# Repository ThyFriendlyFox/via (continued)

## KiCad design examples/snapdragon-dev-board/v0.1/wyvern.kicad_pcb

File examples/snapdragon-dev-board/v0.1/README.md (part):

# Wyvern — board prototype v0.1

> Archived: v0.1 of the [Wyvern prototype series](../README.md), as of commit `04fd430`. The design and KiCad files are the ones that commit holds. The next version, [`../v0.2/`](../v0.2/), makes it one flat board: a QCS6490 module soldered straight on, no sockets.

A development board the size of a Teensy with a Snapdragon on it. The Snapdragon 845 (4 Kryo 385
Gold cores at 2.65 GHz and 4 Silver at 1.77 GHz, an Adreno 630, a Hexagon 685 DSP, 4 GB of LPDDR4X,
32 GB of UFS 2.1, Wi-Fi 5 2x2 and Bluetooth 5) arrives on Lantronix's Open-Q 845 uSOM, a 50 x 25 mm
module that plugs into 3 sockets on top of the board and runs Linux or Android. Under it, an RP2350
drives 30 pins at 3.3 V the way a Teensy's microcontroller does; the Snapdragon resets it, puts it in
its bootloader and talks to it over USB, so Linux flashes it. One USB-C cable powers the board and
carries USB 3.1 and a DisplayPort monitor.

This folder is a whole KiCad 10 project made with the EE Workcenter: `design.py` is the board, and
the `.kicad_*` files beside it are what `workcenter design` writes from it.

| Item | State |
|---|---|
| Schematic | drawn with wires in blocks, the SOM's 300 pins named from its datasheet; ERC <!-- erc -->0 errors, 0 warnings<!-- /erc -->; no parity warning |
| Board | 60.96 x 30.48 mm (2.4 x 1.2 in), **6 layers**, 1.6 mm, black mask, white legend, ENIG, made to Sierra Circuits' Web PCB limits; 2 rows of 24 pins on the 0.1 in grid, 1.1 in apart; the SOM's sockets, USB-C, the RP2350 and its flash on the top face, the power, the microSD and the pinout card on the bottom |
| Gates | <!-- gates -->GREEN with 13 warnings: ERC 0 and 0; DRC 0 errors, 0 unconnected, 0 parity, 7 warnings (silkscreen at the edge, 2 vias with nothing past them); SIM 6 decks, 488 corner runs, 0 failures; EXPORT 4 of 4 (`docs/gates.md`)<!-- /gates --> |
| USB | the USB-C port's 4 SuperSpeed pairs and its USB 2 pair drawn by hand in `design.py` as coupled 90 ohm pairs on the outer layers, each over a ground plane; no pair crosses another or turns over |
| Power | 5 V from USB-C (or the 5V pin) to the SOM's 3.8 V by a TPS62130 buck, 3 A for the module's 8.7 W boot peak; 3.3 V from that by an AP2112K; the SOM's own 1.8 V on a pin |
| Simulation | 6 decks, each at every corner of its parts' tolerances (`sim/`): the 3.8 V rail inside the SOM's window, the Snapdragon's I2C on the pins, the RP2350's reset and boot lines, the USB input's resonance with a cable; a frequency plan holds the 3 clocks against it |
| Parts and cost | an orderable part for every line (`../parts/catalog.csv`); the board's parts $32.76 for 1, $25.71 each for 10, with 4 lines not priced and each reason named; the Snapdragon module is not priced: Digi-Key lists it as obsolete |
| Firmware | none yet |

## Images

With the Snapdragon module on its sockets (`assembly.py` on the workcenter's `tools/scene.py`,
drawn by `workcenter pictures .`), turning once round:

| Assembled | From the USB-C end |
|---|---|
|  |  |

The carrier without the module:

| Top face | Bottom face (mirrored) |
|---|---|
|  |  |

| 3D, from above | 3D, from below |
|---|---|
|  |  |

| Turning, from above | Turning, from below |
|---|---|
|  |  |

| Every layer | The schematic |
|---|---|
|  |  |

From `workcenter pictures .` (its `pictures.json`), with KiCad's 3D bodies in `KICAD10_3DMODEL_DIR`
and the 5 bodies in `models/`.

## What changed in v0.1: the first board

The request: a new microcontroller development board, something like a Teensy but with a Snapdragon
chip, compact, as the workcenter's example of what it can make.

| Finding | The owner's answer | What v0.1 does |
|---|---|---|
| A Snapdragon cannot stand alone on a board this size: it needs LPDDR4X, flash and 3 PMICs, and its 0.4 mm BGA needs microvias and length-matched memory lanes the workcenter's router does not draw | shown the plan (the module on a Teensy-shaped carrier, an RP2350 on the pins) on 2026-11-11; the answer named vape-prototype as the layout to follow, and the work went on | carries the Snapdragon 845 on Lantronix's Open-Q 845 uSOM, whose pinout and land pattern are public ("The Snapdragon module") |
| A Snapdragon's pins run at 1.8 V; a Teensy's at 3.3 V | part of the same plan | an RP2350 drives the pins at 3.3 V; the Snapdragon's own I2C, debug UART, power key and reset are on the pins too, marked 1.8 V ("The RP2350") |

### Board

The SOM's land pattern sets the board: its 3 sockets 23.0 mm apart along its long sides, turned 180
degrees so its power socket (JT2) sits next to USB-C. The pins run outside the module along both long
edges, so the board is the module's width plus 2 rows. Everything a hand touches is on top at the
USB-C end (PWR, BOOT, the Snapdragon's 3 lights and GP25's); the RP2350 and its flash sit under the
module on top; the power, the microSD and the buttons the board rarely needs are on the bottom. The
router (FreeRouting) drew <!-- route -->789 segments and 51 vias round what `design.py` draws by hand: the USB pairs, the RP2350's supplies and its pins fanned out to vias on 3 sides, the crystal's lines, the RGB lines<!-- /route -->.

### Simulation

6 new decks, run at every corner (`workcenter sim .`): SOM_SYS at 3.61 to 3.93 V against the SOM's
3.45 to 4.75 V; the I2C pull-ups' rise time 186 ns against 300 ns with 100 pF on the line; RUN at
48 mV and QSPI_SS at 0.42 V against the RP2350's 0.8 V when the Snapdragon pulls them; the 5 V
input's resonance with a USB-C cable, and the buck's power-save pulses on it. A frequency plan
(`sim/frequency-plan.json`) holds the buck, the RP2350's regulator and its crystal against that
resonance ("Frequency plan").

### Firmware

None yet ("Open items").

### Parts and cost

Every part is new. `../parts/catalog.csv` names an orderable part for each line, read from Digi-Key
on 2026-11-11; `workcenter costs ..` prices the board into `../parts/lists/` ("Bill of materials").

### Verification summary

No verification package yet ("Open items").

## Architecture

```
USB-C (J4) ──VBUS──┬──────────────────────────── 5V pin
                   ├── U1 USBLC6 (D+, D-)
                   └── U2 TPS62130 ── L1 2.2 uH ── SOM_SYS 3.8 V ──┬── SOM JT2 (SOM_SYS_PWR x17)
                                                                    └── U3 AP2112K ── +3V3 ── RP2350, 3V3 pins
USB-C SuperSpeed x4, USB 2 ────────────────────────────────────────────── SOM JT3 (USB3_SS_*, USB3_HS_*)
USB-C CC1, CC2, SBU1, SBU2 ─────────────────────────────────────────────── SOM JT2 (the PMI8998's Type-C)
SOM JT3 USB2_HS ── R6, R7 27 ohm ── U4 RP2350 USB (the RP2350 is a device on the SOM's 2nd port)
SOM JT3 GPIO27, GPIO11 (1.8 V) ── U6, U7 74LVC1G07 ── RUN, QSPI_SS (reset, bootloader)
SOM JT1 SDC2 ── J7 microSD;  SOM JT3 VREG_L21A, VREG_L13A ── its supply and pull-ups
SOM JT1 VREG_S4A ── +1V8 ── 1V8 pin, U6, U7, the I2C pull-ups
U4 RP2350 GP0..GP29 ── the pins
```

### Stackup

| Layer | Copper | Use |
|---|---|---|
| F.Cu | 35 um | parts, the SOM's sockets, 2 SuperSpeed pairs, ground pour |
| In1.Cu | 15 um | ground plane, under F.Cu's pairs (0.21 mm of 7628) |
| In2.Cu | 15 um | signals |
| In3.Cu | 15 um | signals, supplies |
| In4.Cu | 15 um | ground plane, over B.Cu's pairs |
| B.Cu | 35 um | parts, 2 SuperSpeed pairs and the USB 2 pair, ground pour |

A 90 ohm pair on an outer layer is 0.25 mm tracks 0.15 mm apart over 0.21 mm of FR4 (er 4.5), by
IPC-2141's edge-coupled microstrip; its 0.4 mm pitch is the SOM socket's.

## The Snapdragon module

Lantronix's Open-Q 845 uSOM (QC-DB-P10004: 4 GB, 32 GB) carries the SDA845, its LPDDR4X on top of it,
the UFS flash, the PM845, PMI8998 and PM8005 PMICs and a WCN3990 for Wi-Fi and Bluetooth, on
50 x 25 mm. It mates through 3 Hirose DF40C-100DP-0.4V(51) headers underneath; this board carries the
DF40HC(3.0)-100DS-0.4V(51) receptacles for a 3.0 mm stack, so up to 1.5 mm of parts fit under it.
Every pin name in `open_q_845.py` and the 3 symbols in `symbols/wyvern.kicad_sym` is the datasheet's
(PDS-0007 Rev C, Tables 2 to 4); the sockets' places and pin 1 corners are its Figure 7. The
datasheet calls its schematic the controlling document; that needs a development-kit registration.

- **Power.** SOM_SYS_PWR, 3.45 to 4.75 V, typical 3.8 V (Table 7); the module draws 8.7 W at most
  while it boots and 6.9 W with every core loaded (Table 9). USB_VBUS goes to the PMI8998's charger
  input for USB detection; BATT_ID and BATT_THERM are left open, so it sees no battery
  ("Decisions").
- **Its lights.** The PMI8998's RGB current sources drive D1 to D3 straight, with no resistors.
- **Its keys.** PWR (SW1, PHONE_ON_N) and VOL- (SW4, PM_RESIN_VOLDN_N; held with PWR, a hard reset).
  EDL (SW5) holds GPIO57 high through 1k at power-on: the Snapdragon's emergency download over USB.
  CBL_PWR_N is grounded through R15 (0 ohm), so the module starts when power arrives; leave R15 off
  to start it with PWR.
- **Its temperature.** AUX_THERM has a 100k NTC (TH1) under the power stage.

## Power

| Rail | From | To | Set by |
|---|---|---|---|
| VBUS | USB-C or the 5V pin | U2, the SOM's USB_VBUS, U1 | a 5 V, 3 A Type-C supply: the SOM's 8.7 W boot peak is 2.3 A at 3.8 V, about 2 A at 5 V |
| SOM_SYS | U2 TPS62130, L1 2.2 uH | the SOM, U3 | R1 374k over R2 100k: 0.8 V x 4.74 = 3.79 V nominal; 3.61 to 3.93 V at every corner (`sim/`) |
| +3V3 | U3 AP2112K-3.3 | the RP2350, its flash, the 3V3 pins | its 600 mA; 250 mV dropout typical at 600 mA from a 3.6 V or higher input |
| +1V1 | the RP2350's own regulator, L2 3.3 uH | the RP2350's core | Raspberry Pi's layout and parts (Hardware design with RP2350, 2.1) |
| +1V8 | the SOM's VREG_S4A | the 1V8 pin, U6, U7, R16, R17 | the SOM; 600 mA for the carrier (Table 2) |
| SD_VDD, SD_VIO | the SOM's VREG_L21A and VREG_L13A | the microSD, its pull-ups | the SOM; 800 mA for the card (Table 4) |

The 5V pin is VBUS itself: power the board from USB-C or from the pin, not both. A 5 V supply on the
pin with a computer on USB-C feeds that computer's port.

## USB-C

J4 is Amphenol's 12401610E4#2A, a USB 3.1 Gen 2 receptacle with both rows on the top layer, its front
face 1.0 mm past the board's edge. The SOM's Type-C port (the PMI8998 handles CC and orientation)
gives USB 3.1, USB 2 and DisplayPort over the same pins.

It is wired the way a plug turned over sees it: the SOM's lane 0 (TX0, RX0) on the receptacle's
second SuperSpeed pins (TX2, RX2), lane 1 on the first, CC1 on B5 and CC2 on A5, SBU swapped to
match. A plug in either orientation still meets the lane its CC pin selects. The point is the layout:
so wired, each layer carries 1 pair to each end of the receptacle, and no 2 pairs on a layer cross.

| Pair | SOM pins (JT3) | Receptacle | Layer |
|---|---|---|---|
| SS_TX1 | 93 (P), 91 (N) | A2, A3 | F.Cu: the inner row into the gap between JT3's rows, west, north, west |
| SS_RX0 | 94 (P), 92 (N) | A11, A10 | F.Cu: the outer row into the gap, west, north, west |
| SS_RX1 | 97 (P), 99 (N) | B11, B10 | B.Cu through 2 vias north of JT3; vias in front of the B row |
| SS_TX0 | 100 (P), 98 (N) | B2, B3 | B.Cu through 2 vias south of JT3 |
| USB_D | 86 (P), 88 (N) | A6, A7; B6, B7 | B.Cu to 2 vias behind the A row; B6 on B.Cu, B7 on In2 |

Every pair keeps P on the same side the whole way: a USB 3 receiver can turn a pair round, a
DisplayPort lane need not. The B row's 12 pads reach 12 vias in 2 staggered columns in front of it,
0.9 mm apart, each 0.69 mm or more from its neighbours' holes on every inner layer (Sierra's 13 mil).
U1, a USBLC6-2SC6, clamps D+ and D- inside the top layer's pairs.

## The RP2350

U4, an RP2350A (QFN-60), with a 16 MB W25Q128JV (U5), the ABM8-272-T3 crystal and the 3.3 uH
inductor Raspberry Pi tuned its oscillator and its core regulator to, and their resistors and
capacitors as Raspberry Pi's minimal design has them. It sits under the module, where everything is
1.0 mm tall or less. The crystal, its 2 load capacitors and XOUT's 1k are on the back, under the
chip's south edge: on top they stood 0.6 mm from 7 of its pins and left them no way out. Each 100 nF
faces its supply pin with its supply pad.

- **USB.** Its USB pins, through R6 and R7 (27 ohm), go to the SOM's second USB port (USB2_HS on
  JT3), a host. Linux sees the RP2350 as a device: its bootloader as a drive, then whatever its
  firmware is.
- **Reset and bootloader.** RUN and QSPI_SS each have a 10k pull-up and the RP2350's own (32k at
  least). The Snapdragon pulls them through U6 and U7, 74LVC1G07 open-drain buffers on its 1.8 V,
  from its GPIO27 and GPIO11; R10 and R11 (100k) hold the buffers off while the module is off. RUN
  (SW3) and BOOT (SW2) do the same by hand. Hold BOOT and press RUN, or let the Snapdragon do it:
  the RP2350 comes up as a drive.
- **SWD.** SWCLK and SWDIO on 2 pads on the bottom (TP1, TP2).

## Pin plan

Every GPIO of the RP2350 is on a pin; functions from its datasheet's function table (F1 SPI, F2
UART, F3 I2C, F4 PWM; section 1.2.3). GP12 to GP19 also carry HSTX, the RP2350's high-speed serial
output (DVI). The header's pins count from the USB-C end.

| GPIO | RP2350 pin | Header | Functions (F1 to F4) | Also |
|---|---|---|---|---|
| GP0 | 2 | bottom 2 | SPI0 RX, UART0 TX, I2C0 SDA, PWM0 A |  |
| GP1 | 3 | bottom 3 | SPI0 CSn, UART0 RX, I2C0 SCL, PWM0 B |  |
| GP2 | 4 | bottom 4 | SPI0 SCK, UART0 CTS, I2C1 SDA, PWM1 A |  |
| GP3 | 5 | bottom 5 | SPI0 TX, UART0 RTS, I2C1 SCL, PWM1 B |  |
| GP4 | 7 | bottom 6 | SPI0 RX, UART1 TX, I2C0 SDA, PWM2 A |  |
| GP5 | 8 | bottom 7 | SPI0 CSn, UART1 RX, I2C0 SCL, PWM2 B |  |
| GP6 | 9 | bottom 8 | SPI0 SCK, UART1 CTS, I2C1 SDA, PWM3 A |  |
| GP7 | 10 | bottom 9 | SPI0 TX, UART1 RTS, I2C1 SCL, PWM3 B |  |
| GP8 | 12 | bottom 10 | SPI1 RX, UART1 TX, I2C0 SDA, PWM4 A |  |
| GP9 | 13 | bottom 11 | SPI1 CSn, UART1 RX, I2C0 SCL, PWM4 B |  |
| GP10 | 14 | bottom 12 | SPI1 SCK, UART1 CTS, I2C1 SDA, PWM5 A |  |
| GP11 | 15 | bottom 13 | SPI1 TX, UART1 RTS, I2C1 SCL, PWM5 B |  |
| GP12 | 16 | bottom 14 | SPI1 RX, UART0 TX, I2C0 SDA, PWM6 A | HSTX (DVI) |
| GP13 | 17 | bottom 15 | SPI1 CSn, UART0 RX, I2C0 SCL, PWM6 B | HSTX (DVI) |
| GP14 | 18 | bottom 16 | SPI1 SCK, UART0 CTS, I2C1 SDA, PWM7 A | HSTX (DVI) |
| GP15 | 19 | bottom 17 | SPI1 TX, UART0 RTS, I2C1 SCL, PWM7 B | HSTX (DVI) |
| GP16 | 27 | bottom 18 | SPI0 RX, UART0 TX, I2C0 SDA, PWM0 A | HSTX (DVI) |
| GP17 | 28 | bottom 19 | SPI0 CSn, UART0 RX, I2C0 SCL, PWM0 B | HSTX (DVI) |
| GP18 | 29 | bottom 20 | SPI0 SCK, UART0 CTS, I2C1 SDA, PWM1 A | HSTX (DVI) |
| GP19 | 31 | bottom 21 | SPI0 TX, UART0 RTS, I2C1 SCL, PWM1 B | HSTX (DVI) |
| GP20 | 32 | top 22 | SPI0 RX, UART1 TX, I2C0 SDA, PWM2 A |  |
| GP21 | 33 | top 21 | SPI0 CSn, UART1 RX, I2C0 SCL, PWM2 B |  |
| GP22 | 34 | top 20 | SPI0 SCK, UART1 CTS, I2C1 SDA, PWM3 A |  |
| GP23 | 35 | top 19 | SPI0 TX, UART1 RTS, I2C1 SCL, PWM3 B |  |
| GP24 | 36 | top 18 | SPI1 RX, UART1 TX, I2C0 SDA, PWM4 A |  |
| GP25 | 37 | top 17 | SPI1 CSn, UART1 RX, I2C0 SCL, PWM4 B | LED D4 through R12 |
| GP26 | 40 | top 16 | SPI1 SCK, UART1 CTS, I2C1 SDA, PWM5 A | ADC0 |
| GP27 | 41 | top 15 | SPI1 TX, UART1 RTS, I2C1 SCL, PWM5 B | ADC1 |
| GP28 | 42 | top 14 | SPI1 RX, UART0 TX, I2C0 SDA, PWM6 A | ADC2 |
| GP29 | 43 | top 13 | SPI1 CSn, UART0 RX, I2C0 SCL, PWM6 B | ADC3 |

The other pins:

| Pin | Top row | Bottom row |
|---|---|---|
| 1 | GND | GND |
| 2 | 5V (VBUS) | GP0 |
| 3 | 3V3 | GP1 |
| 4 | GND | GP2 |
| 5 | PWR: the SOM's power key, active low (1.8 V) | GP3 |
| 6 | RST: the SOM's RESIN, active low (1.8 V) | GP4 |
| 7 | 1V8: the SOM's VREG_S4A | GP5 |
| 8 | SDA: the Snapdragon's I2C (QUP10), 1.8 V, 2.2k pull-up | GP6 |
| 9 | SCL, 1.8 V, 2.2k pull-up | GP7 |
| 10 | TX: the Snapdragon's debug UART (QUP9), 1.8 V | GP8 |
| 11 | RX, 1.8 V | GP9 |
| 12 | GND | GP10 |
| 13 to 22 | GP29 to GP20 | GP11 to GP19, GND (22) |
| 23 | 3V3 | RUN: the RP2350's reset, active low |
| 24 | GND | GND |

The 1.8 V pins are the Snapdragon's own and are not 3.3 V tolerant.

## Datasheets, models and simulation

The datasheets the design reads, each named where it is used:

| Part | Document |
|---|---|
| Open-Q 845 uSOM | Lantronix PDS-0007 Rev C (April 2022), cdn.lantronix.com |
| TPS62130 | TI SLVSAG7F (November 2021) |
| RP2350 | Raspberry Pi RP2350 Datasheet; Hardware design with RP2350 |
| SN74LVC1G07 | TI SCES296AG (October 2025) |
| 12401610E4#2A | Amphenol Commercial Products' USB Type-C cut sheet (the 9.59 mm from the face to the pegs) |
| I2C | NXP UM10204 Rev. 7.0 |

The decks in `sim/` stand in for the parts with their datasheets' numbers, at every corner of the
board's 1 % resistors, C1 and C2 at 50 % either way and a cable from 0.5 to 1.5 m
(`sim/corners.json`, 32 Monte Carlo runs each):

| Deck | What it proves | Result |
|---|---|---|
| `sys_rail_low.cir` | SOM_SYS with the TPS62130's reference at 781.6 mV and FB's 100 nA out of the pin | 3.67 V; 3.61 V at the lowest corner, in 3.45 to 4.75 V |
| `sys_rail_high.cir` | the same at 822.4 mV and 100 nA in | 3.94 V at the highest corner, in 3.45 to 4.75 V |
| `som_i2c.cir` | the Snapdragon's I2C on the pins, 2.2k to 1.8 V, 100 pF | rise 186 ns (300 ns allowed); low 0.14 V at 0.76 mA |
| `mcu_control.cir` | RUN and QSPI_SS pulled by U6, U7 and BOOT | RUN 48 mV; QSPI_SS 0.42 V by U7, 0.38 V by BOOT (0.8 V allowed) |
| `vbus_pdn.cir` | the 5 V input's impedance: a USB-C cable with C1 and C2 | a peak of 0.74 ohm at 41 kHz, Q 3.9; 2.17 ohm at the worst corner, under the buck's 2.29 ohm |
| `vbus_psm.cir` | the buck's power-save pulses at that resonance | 5.1 mV of ripple; 10.5 mV at the worst corner (50 mV allowed) |

### Frequency plan

`sim/frequency-plan.json` (workcenter PROCESSES.md P30); `workcenter sim .` holds each source's first
10 harmonics against each resonance's band.

| Source | Frequency | From |
|---|---|---|
| TPS62130 | 2.5 MHz in PWM; in power save, a rate that falls with the load to 2 kHz | SLVSAG7F 8.4.1, 8.4.2 |
| RP2350 core regulator | 3 MHz | RP2350 datasheet, Table 1689 |
| RP2350 crystal | 12 MHz | Y1 |

| Resonance | Frequency over the corners | Band held |
|---|---|---|
| VBUS behind a USB-C cable (`vbus_pdn.cir`) | 27.4 to 82.2 kHz, Q 2.5 to 6.5 | 21.9 to 98.7 kHz |

The buck in power save passes through that band, so the plan answers the overlap with `vbus_psm.cir`:
each pulse draws 33 nC, and the input moves 10.5 mV at most. The buck's input is also a negative
resistance, VIN squared over its power: 2.29 ohm at the module's boot peak from USB's 4.75 V. The
cable's peak stays under it at every corner, with 0.13 ohm to spare when the cable is 1.5 m and C1
and C2 are at their low end ("Open items").

The plan leaves out the module's own regulators (the PM845's and PMI8998's frequencies are not in the
public datasheet) and the resonances of SOM_SYS, +3V3 and +1V1: each is a regulator's closed-loop
output, and none of the 3 makers publishes its output impedance.

## Bill of materials

| Ref | Value | Package | Face | Part |
|---|---|---|---|---|
| C1 | 10u | C_0805_2012Metric | bottom | Murata GRM21BR61C106KE15L |
| C2 | 10u | C_0805_2012Metric | bottom | Murata GRM21BR61C106KE15L |
| C3 | 22u | C_0805_2012Metric | bottom | Murata GRM21BR61A226ME51L |
| C4 | 22u | C_0805_2012Metric | bottom | Murata GRM21BR61A226ME51L |
| C5 | 22u | C_0805_2012Metric | bottom | Murata GRM21BR61A226ME51L |
| C6 | 3.3n | C_0402_1005Metric | bottom | Murata GRM155R71H332KA01D |
| C7 | 1u | C_0402_1005Metric | bottom | Murata GRM155R61A105KE15D |
| C8 | 1u | C_0402_1005Metric | bottom | Murata GRM155R61A105KE15D |
| C9 | 4.7u | C_0402_1005Metric | top | Murata GRM155R61A475MEAAD |
| C10 | 4.7u | C_0402_1005Metric | top | Murata GRM155R61A475MEAAD |
| C11 | 4.7u | C_0402_1005Metric | top | Murata GRM155R61A475MEAAD |
| C12 | 100n | C_0402_1005Metric | top | Murata GRM155R71C104KA88D |
| C13 | 100n | C_0402_1005Metric | top | Murata GRM155R71C104KA88D |
| C14 | 100n | C_0402_1005Metric | top | Murata GRM155R71C104KA88D |
| C15 | 100n | C_0402_1005Metric | top | Murata GRM155R71C104KA88D |
| C16 | 100n | C_0402_1005Metric | top | Murata GRM155R71C104KA88D |
| C17 | 100n | C_0402_1005Metric | top | Murata GRM155R71C104KA88D |
| C18 | 100n | C_0402_1005Metric | top | Murata GRM155R71C104KA88D |
| C19 | 100n | C_0402_1005Metric | top | Murata GRM155R71C104KA88D |
| C20 | 15p | C_0402_1005Metric | bottom | Murata GRM1555C1H150JA01D |
| C21 | 15p | C_0402_1005Metric | bottom | Murata GRM1555C1H150JA01D |
| C22 | 100n | C_0402_1005Metric | top | Murata GRM155R71C104KA88D |
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
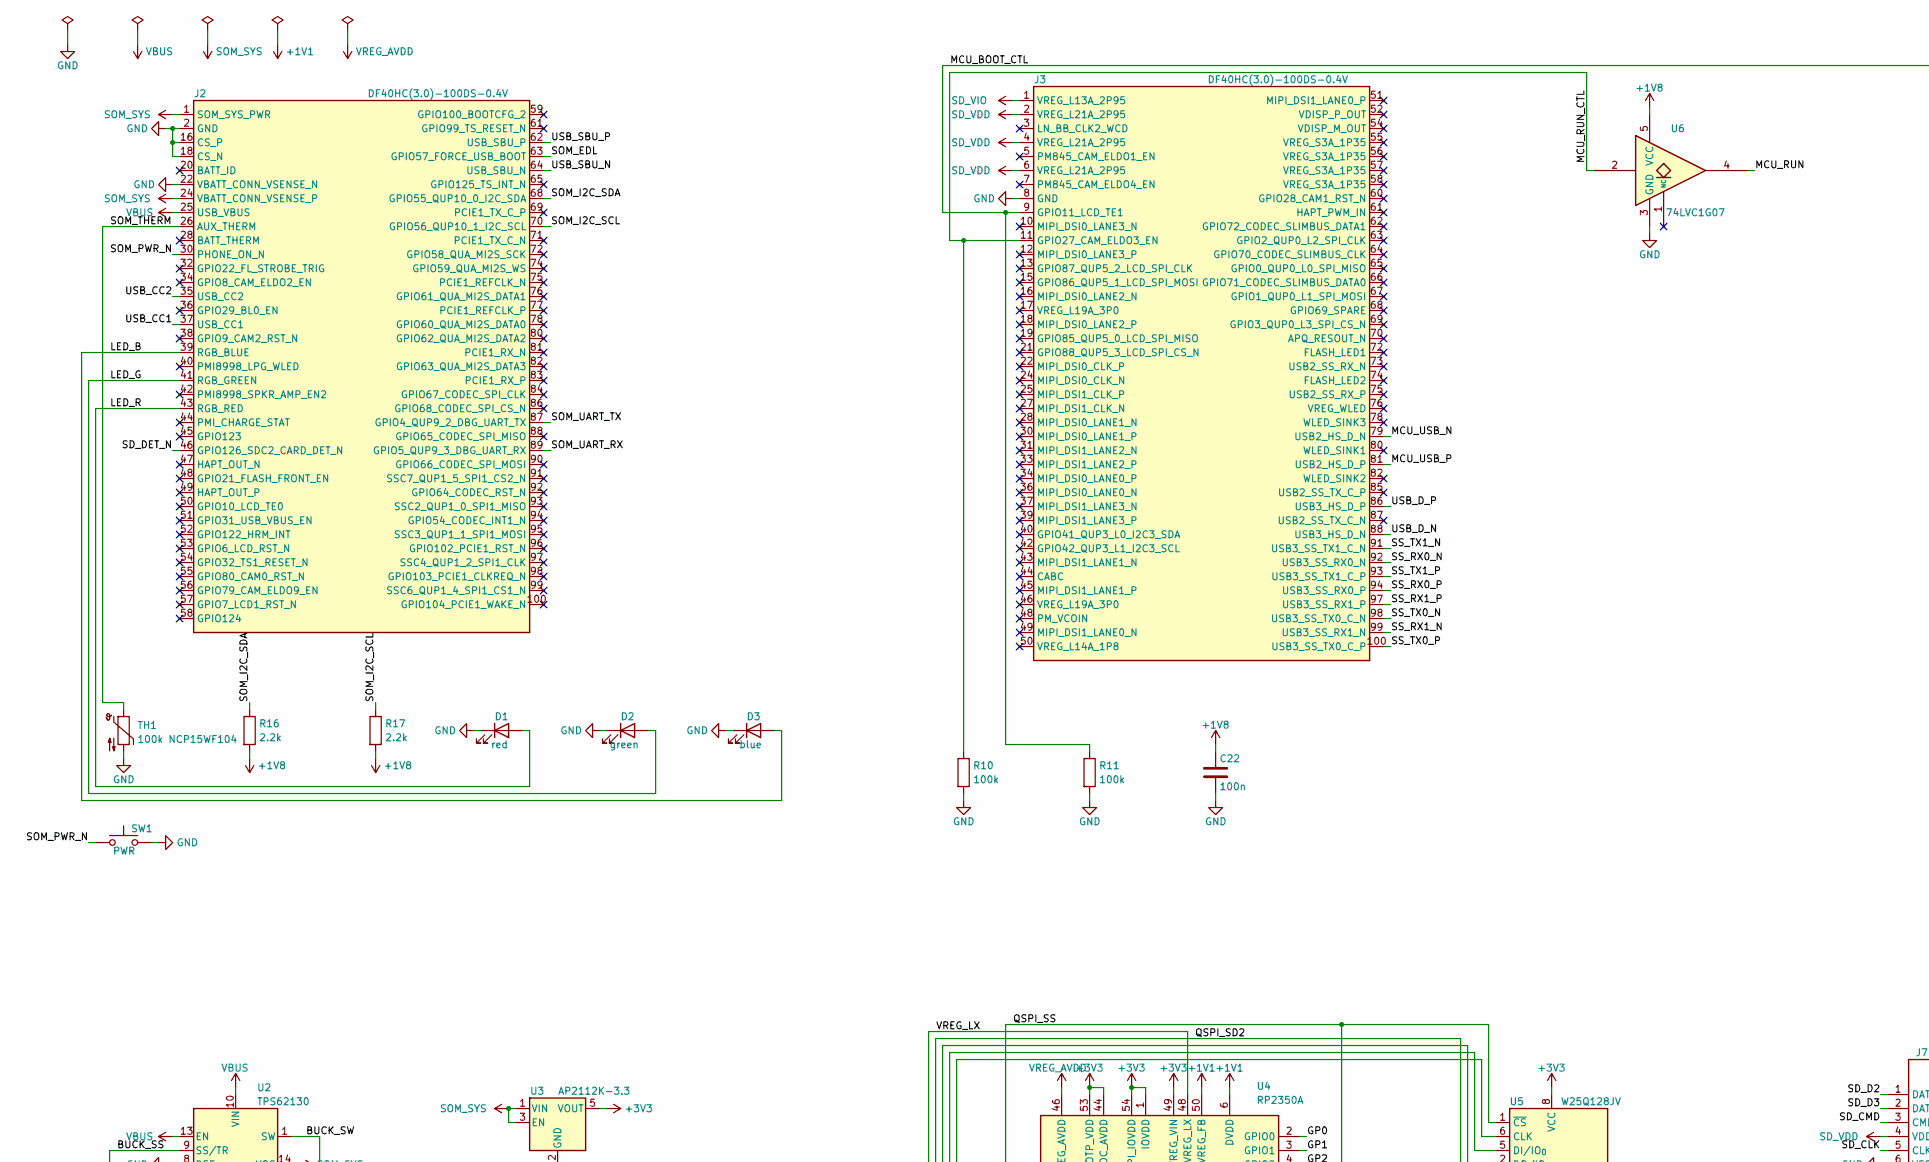
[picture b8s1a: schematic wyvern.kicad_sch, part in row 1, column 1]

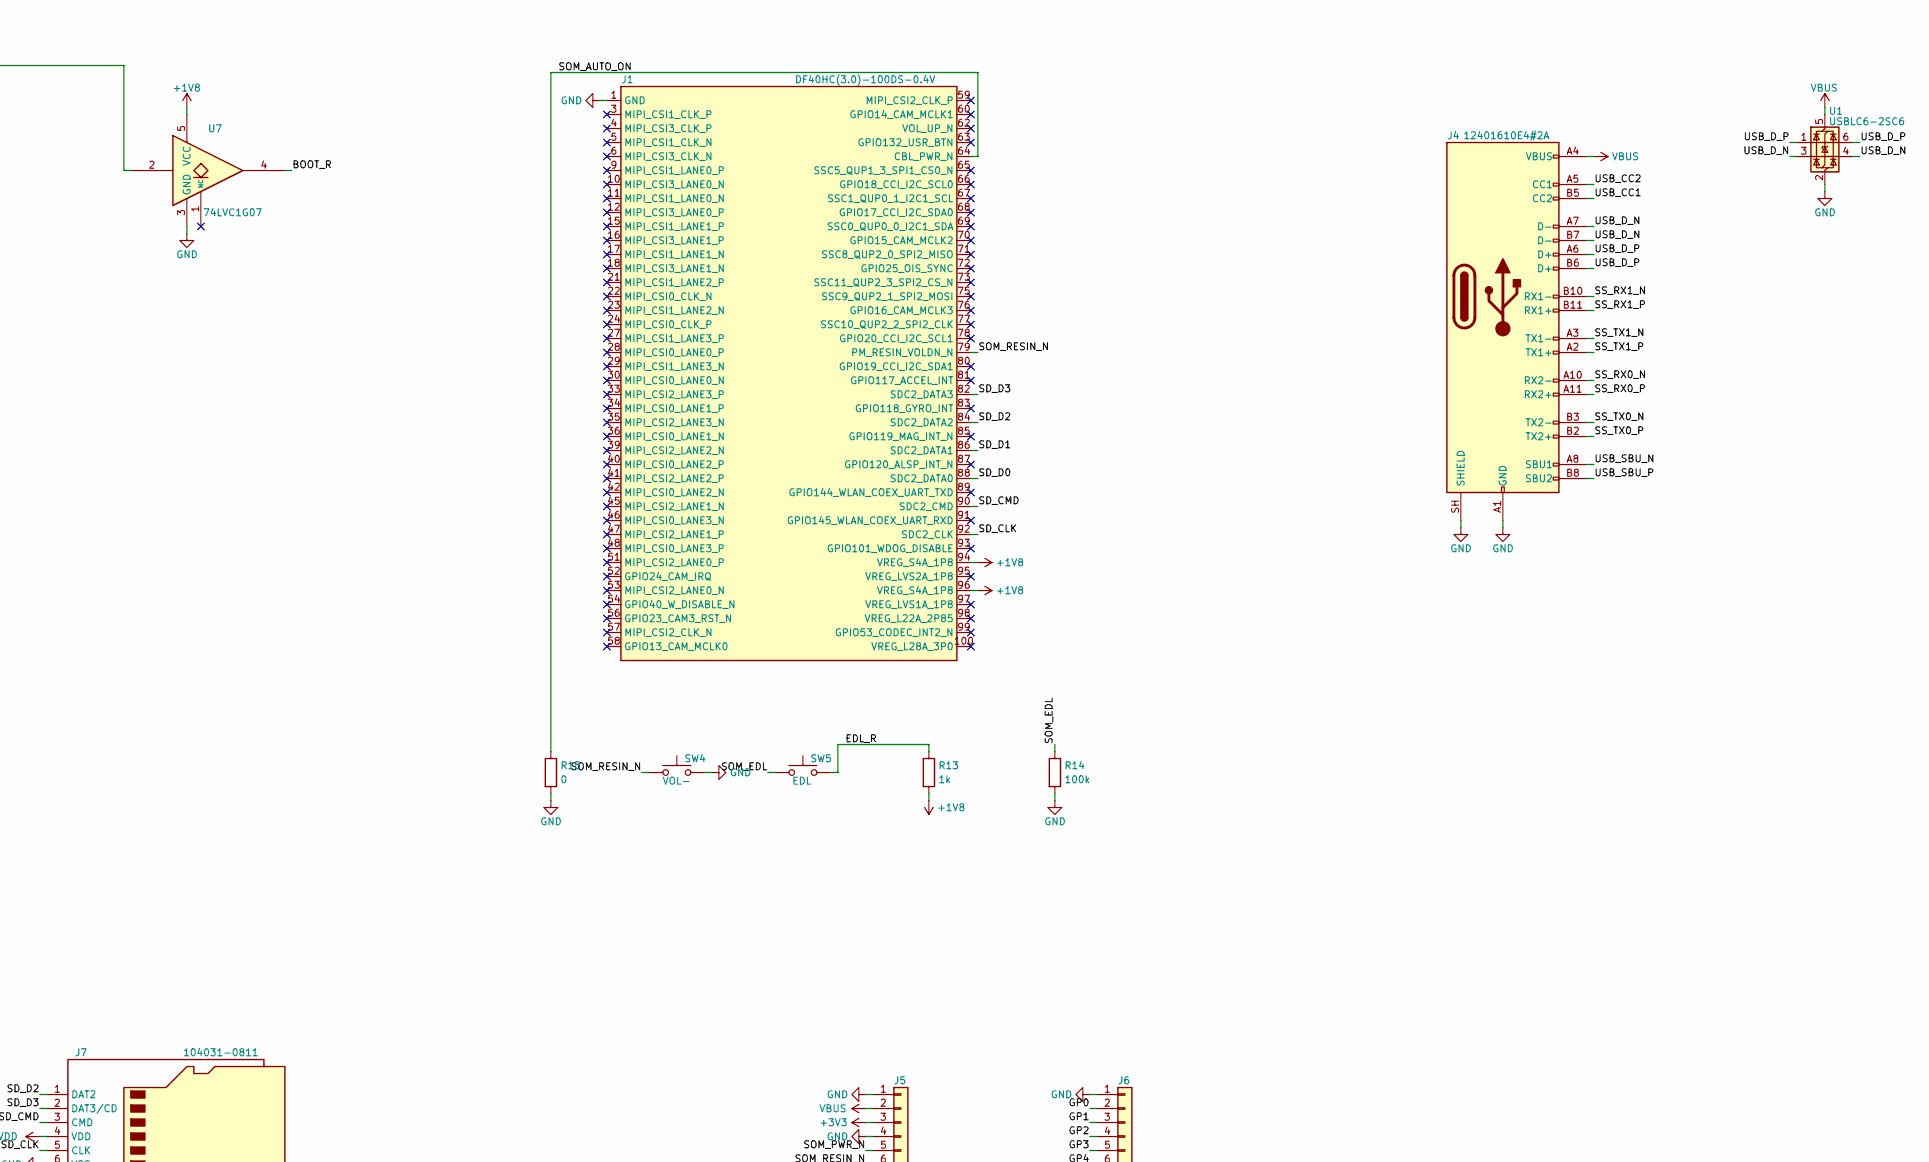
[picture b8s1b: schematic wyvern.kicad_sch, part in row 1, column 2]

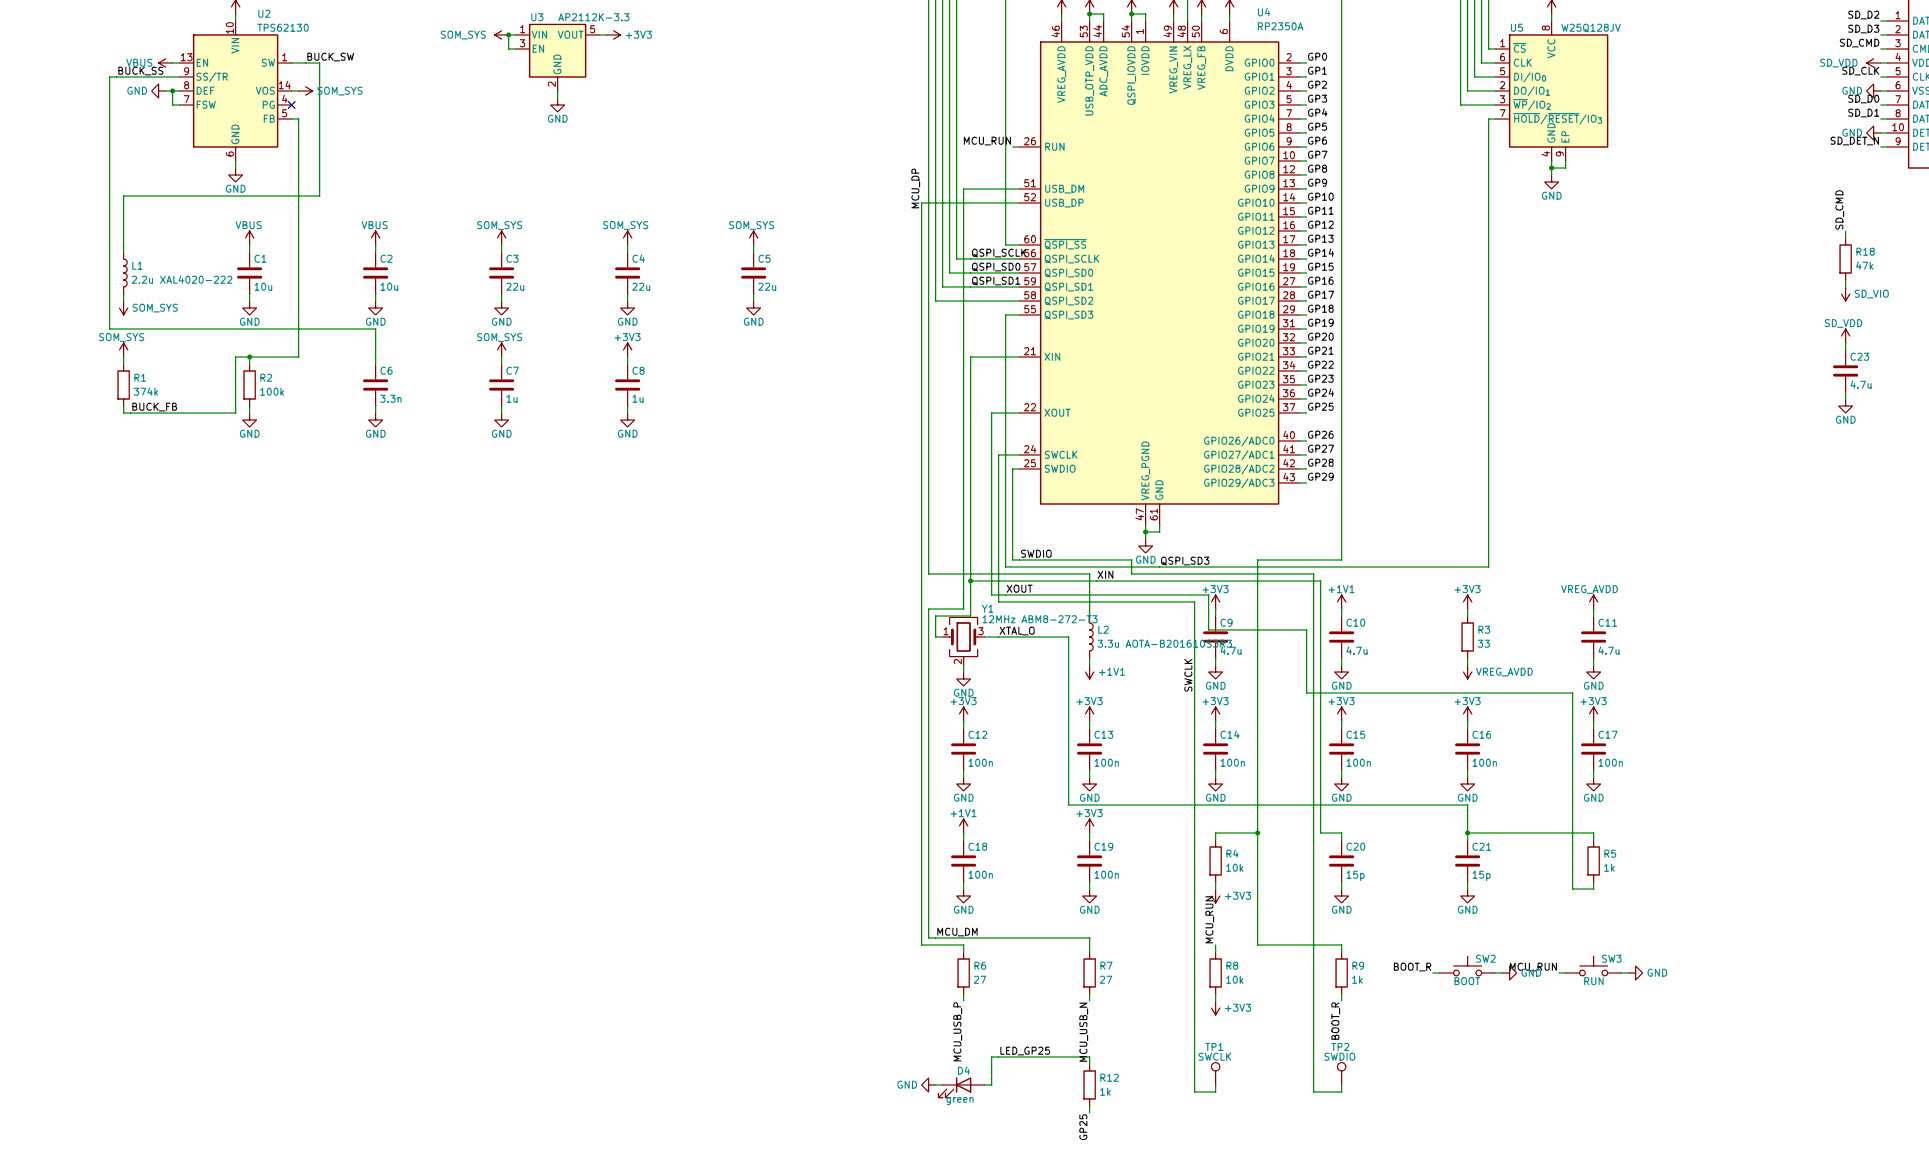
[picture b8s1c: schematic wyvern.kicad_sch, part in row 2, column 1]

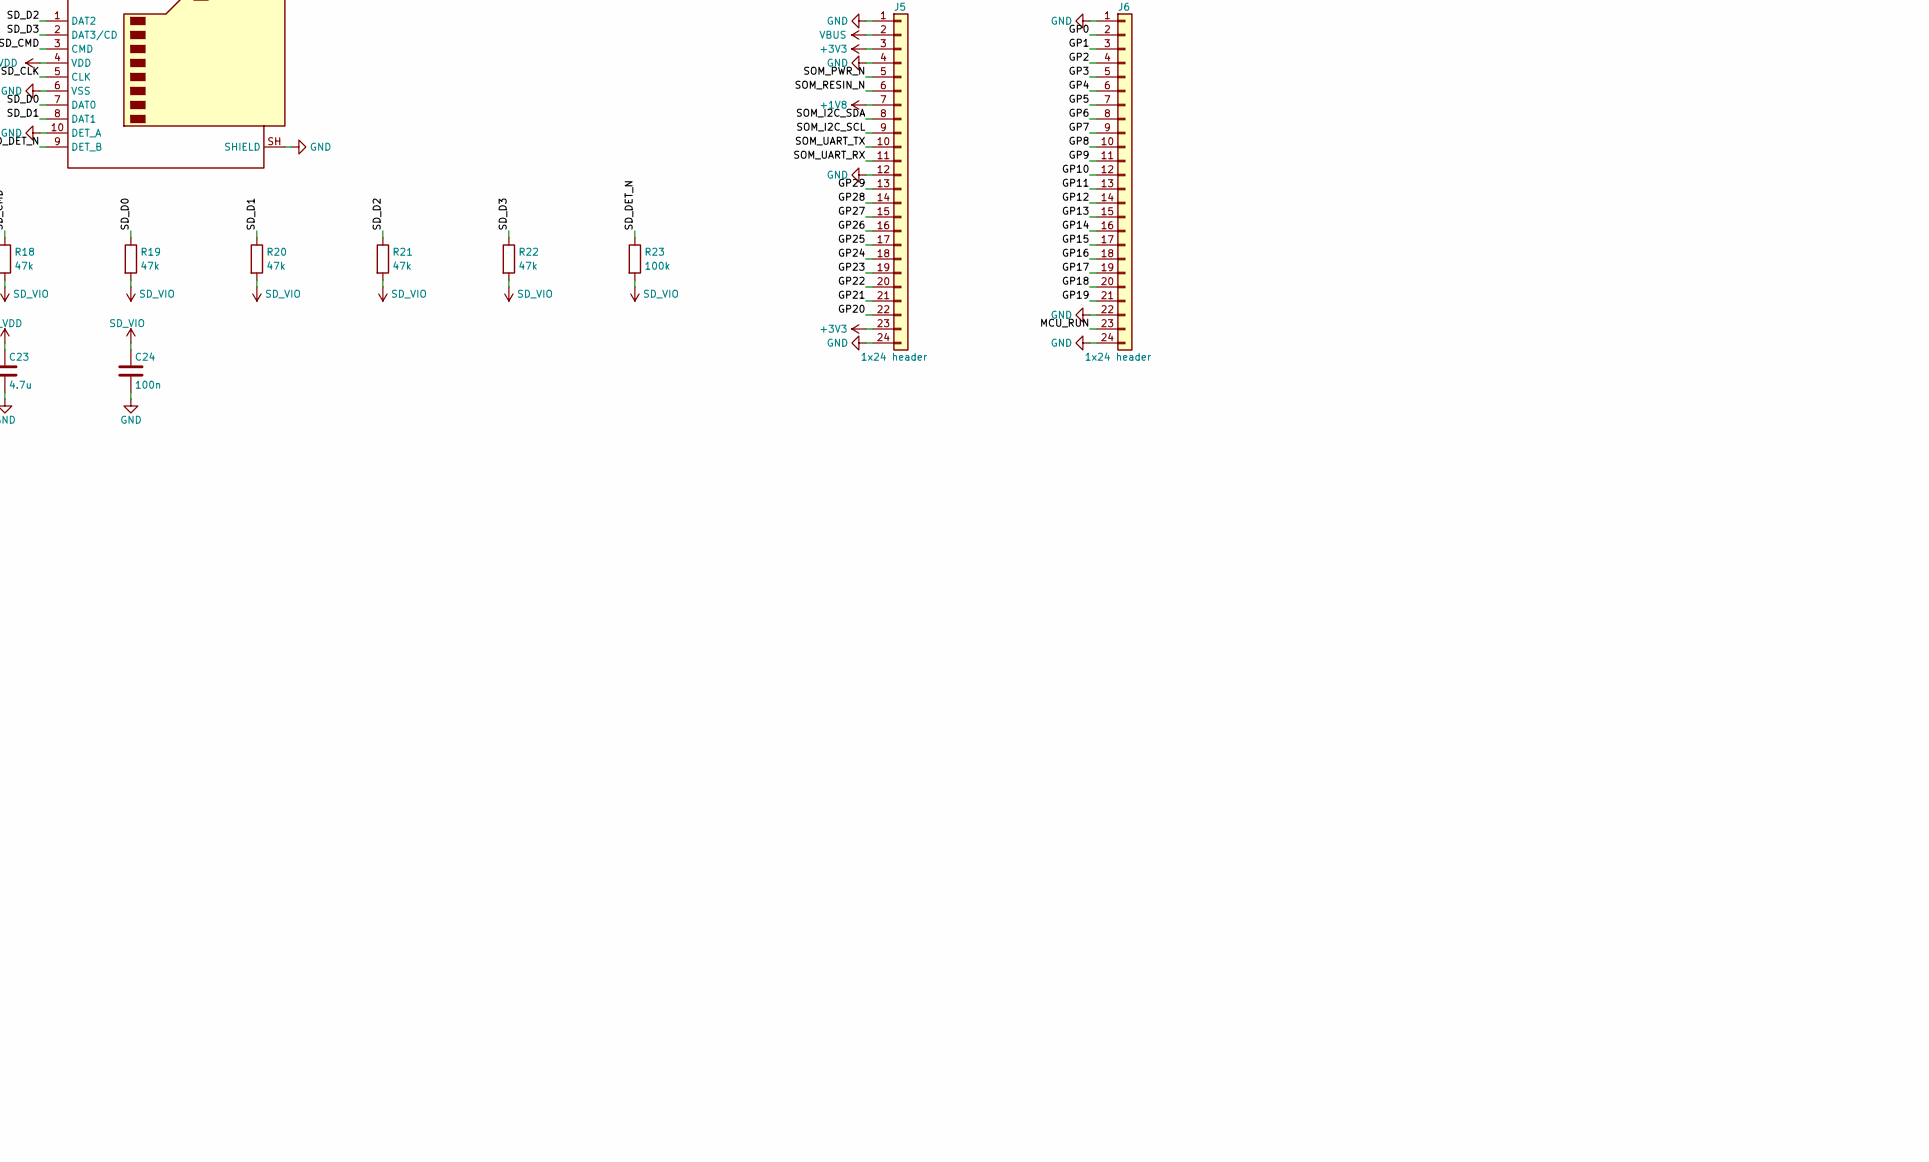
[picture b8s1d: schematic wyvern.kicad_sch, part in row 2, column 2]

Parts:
C1, C2: 10u; C_0805_2012Metric
C3, C4, C5: 22u; C_0805_2012Metric
C6: 3.3n; C_0402_1005Metric
C7, C8: 1u; C_0402_1005Metric
C9, C10, C11: 4.7u; C_0402_1005Metric
C12, C13, C14, C15, C16, C17, C18, C19, C22, C24: 100n; C_0402_1005Metric
C20, C21: 15p; C_0402_1005Metric
C23: 4.7u; C_0603_1608Metric
D1: red; LED_0603_1608Metric
D2, D4: green; LED_0603_1608Metric
D3: blue; LED_0603_1608Metric
J1, J2, J3: DF40HC(3.0)-100DS-0.4V; Hirose_DF40HC(3.0)-100DS-0.4V_2x50_P0.4mm_SOM
J4: 12401610E4#2A; USB_C_Receptacle_Amphenol_12401610E4-2A_Ring6mil
J5, J6: 1x24 header; PinHeader_1x24_P2.54mm_Vertical
J7: 104031-0811; microSD_HC_Molex_104031-0811
L1: 2.2u XAL4020-222; L_Coilcraft_XAL4020-XXX
L2: 3.3u AOTA-B201610S3R3; L_Abracon_AOTA-B201610S
R1: 374k; R_0402_1005Metric
R2, R10, R11, R14, R23: 100k; R_0402_1005Metric
R3: 33; R_0402_1005Metric
R4, R8: 10k; R_0402_1005Metric
R5, R9, R12, R13: 1k; R_0402_1005Metric
R6, R7: 27; R_0402_1005Metric
R15: 0; R_0402_1005Metric
R16, R17: 2.2k; R_0402_1005Metric
R18, R19, R20, R21, R22: 47k; R_0402_1005Metric
SW1: PWR; SW_Push_1P1T_NO_CK_KMR2
SW2: BOOT; SW_Push_1P1T_NO_CK_KMR2
SW3: RUN; SW_Push_1P1T_NO_CK_KMR2
SW4: VOL-; SW_Push_1P1T_NO_CK_KMR2
SW5: EDL; SW_Push_1P1T_NO_CK_KMR2
TH1: 100k NCP15WF104; R_0402_1005Metric
TP1: SWCLK; TestPoint_Pad_D1.0mm
TP2: SWDIO; TestPoint_Pad_D1.0mm
U1: USBLC6-2SC6; SOT-23-6
U2: TPS62130; VQFN-16-1EP_3x3mm_P0.5mm_EP1.68x1.68mm
U3: AP2112K-3.3; SOT-23-5
U4: RP2350A; QFN-60-1EP_7x7mm_P0.4mm_EP3.4x3.4mm
U5: W25Q128JV; WSON-8-1EP_6x5mm_P1.27mm_EP3.4x4.3mm
U6, U7: 74LVC1G07; SOT-353_SC-70-5
Y1: 12MHz ABM8-272-T3; Crystal_SMD_3225-4Pin_3.2x2.5mm

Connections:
+1V1: C10.1, C18.1, L2.2, U4.6 (DVDD), U4.23 (DVDD), U4.39 (DVDD), U4.50 (VREG_FB)
+1V8: C22.1, J1.94 (VREG_S4A_1P8), J1.96 (VREG_S4A_1P8), J5.7, R13.2, R16.2, R17.2, U6.5 (VCC), U7.5 (VCC)
+3V3: C8.1, C9.1, C12.1, C13.1, C14.1, C15.1, C16.1, C17.1, C19.1, J5.3, J5.23, R3.1, R4.2, R8.2, U3.5 (VOUT), U4.1 (IOVDD), U4.11 (IOVDD), U4.20 (IOVDD), U4.30 (IOVDD), U4.38 (IOVDD), U4.44 (ADC_AVDD), U4.45 (IOVDD), U4.49 (VREG_VIN), U4.53 (USB_OTP_VDD), U4.54 (QSPI_IOVDD), U5.8 (VCC)
/BOOT_R: R9.2, SW2.1, U7.4
/BUCK_FB: R1.2, R2.1, U2.5 (FB)
/BUCK_SS: C6.1, U2.9 (SS/TR)
/BUCK_SW: L1.1, U2.1 (SW), U2.2 (SW), U2.3 (SW)
/EDL_R: R13.1, SW5.2
/GP0: J6.2, U4.2 (GPIO0)
/GP1: J6.3, U4.3 (GPIO1)
/GP2: J6.4, U4.4 (GPIO2)
/GP3: J6.5, U4.5 (GPIO3)
/GP4: J6.6, U4.7 (GPIO4)
/GP5: J6.7, U4.8 (GPIO5)
/GP6: J6.8, U4.9 (GPIO6)
/GP7: J6.9, U4.10 (GPIO7)
/GP8: J6.10, U4.12 (GPIO8)
/GP9: J6.11, U4.13 (GPIO9)
/GP10: J6.12, U4.14 (GPIO10)
/GP11: J6.13, U4.15 (GPIO11)
/GP12: J6.14, U4.16 (GPIO12)
/GP13: J6.15, U4.17 (GPIO13)
/GP14: J6.16, U4.18 (GPIO14)
/GP15: J6.17, U4.19 (GPIO15)
/GP16: J6.18, U4.27 (GPIO16)
/GP17: J6.19, U4.28 (GPIO17)
/GP18: J6.20, U4.29 (GPIO18)
/GP19: J6.21, U4.31 (GPIO19)
/GP20: J5.22, U4.32 (GPIO20)
/GP21: J5.21, U4.33 (GPIO21)
/GP22: J5.20, U4.34 (GPIO22)
/GP23: J5.19, U4.35 (GPIO23)
/GP24: J5.18, U4.36 (GPIO24)
/GP25: J5.17, R12.2, U4.37 (GPIO25)
/GP26: J5.16, U4.40 (GPIO26/ADC0)
/GP27: J5.15, U4.41 (GPIO27/ADC1)
/GP28: J5.14, U4.42 (GPIO28/ADC2)
/GP29: J5.13, U4.43 (GPIO29/ADC3)
/LED_B: D3.2 (A), J2.39 (RGB_BLUE)
/LED_G: D2.2 (A), J2.41 (RGB_GREEN)
/LED_GP25: D4.2 (A), R12.1
/LED_R: D1.2 (A), J2.43 (RGB_RED)
/MCU_BOOT_CTL: J3.9 (GPIO11_LCD_TE1), R11.1, U7.2
/MCU_DM: R7.1, U4.51 (USB_DM)
/MCU_DP: R6.1, U4.52 (USB_DP)
/MCU_RUN: J6.23, R8.1, SW3.1, U4.26 (RUN), U6.4
/MCU_RUN_CTL: J3.11 (GPIO27_CAM_ELDO3_EN), R10.1, U6.2
/MCU_USB_N: J3.79 (USB2_HS_D_N), R7.2
/MCU_USB_P: J3.81 (USB2_HS_D_P), R6.2
/QSPI_SCLK: U4.56 (QSPI_SCLK), U5.6 (CLK)
/QSPI_SD0: U4.57 (QSPI_SD0), U5.5 (DI/IO_{0})
/QSPI_SD1: U4.59 (QSPI_SD1), U5.2 (DO/IO_{1})
/QSPI_SD2: U4.58 (QSPI_SD2), U5.3 (~WP/IO_{2})
/QSPI_SD3: U4.55 (QSPI_SD3), U5.7 (~HOLD/~RESET/IO_{3})
/QSPI_SS: R4.1, R9.1, U4.60 (~QSPI_SS), U5.1 (~CS)
/SD_CLK: J1.92 (SDC2_CLK), J7.5 (CLK)
/SD_CMD: J1.90 (SDC2_CMD), J7.3 (CMD), R18.1
/SD_D0: J1.88 (SDC2_DATA0), J7.7 (DAT0), R19.1
/SD_D1: J1.86 (SDC2_DATA1), J7.8 (DAT1), R20.1
/SD_D2: J1.84 (SDC2_DATA2), J7.1 (DAT2), R21.1
/SD_D3: J1.82 (SDC2_DATA3), J7.2 (DAT3/CD), R22.1
/SD_DET_N: J2.46 (GPIO126_SDC2_CARD_DET_N), J7.9 (DET_B), R23.1
/SOM_AUTO_ON: J1.64 (CBL_PWR_N), R15.1
/SOM_EDL: J2.63 (GPIO57_FORCE_USB_BOOT), R14.1, SW5.1
/SOM_I2C_SCL: J2.70 (GPIO56_QUP10_1_I2C_SCL), J5.9, R17.1
/SOM_I2C_SDA: J2.68 (GPIO55_QUP10_0_I2C_SDA), J5.8, R16.1
/SOM_PWR_N: J2.30 (PHONE_ON_N), J5.5, SW1.1
/SOM_RESIN_N: J1.79 (PM_RESIN_VOLDN_N), J5.6, SW4.1
/SOM_THERM: J2.26 (AUX_THERM), TH1.1
/SOM_UART_RX: J2.89 (GPIO5_QUP9_3_DBG_UART_RX), J5.11
/SOM_UART_TX: J2.87 (GPIO4_QUP9_2_DBG_UART_TX), J5.10
/SS_RX0_N: J3.92 (USB3_SS_RX0_N), J4.A10 (RX2-)
/SS_RX0_P: J3.94 (USB3_SS_RX0_P), J4.A11 (RX2+)
/SS_RX1_N: J3.99 (USB3_SS_RX1_N), J4.B10 (RX1-)
/SS_RX1_P: J3.97 (USB3_SS_RX1_P), J4.B11 (RX1+)
/SS_TX0_N: J3.98 (USB3_SS_TX0_C_N), J4.B3 (TX2-)
/SS_TX0_P: J3.100 (USB3_SS_TX0_C_P), J4.B2 (TX2+)
/SS_TX1_N: J3.91 (USB3_SS_TX1_C_N), J4.A3 (TX1-)
/SS_TX1_P: J3.93 (USB3_SS_TX1_C_P), J4.A2 (TX1+)
/SWCLK: TP1.1, U4.24 (SWCLK)
/SWDIO: TP2.1, U4.25 (SWDIO)
/USB_CC1: J2.37 (USB_CC1), J4.B5 (CC2)
/USB_CC2: J2.35 (USB_CC2), J4.A5 (CC1)
/USB_D_N: J3.88 (USB3_HS_D_N), J4.A7 (D-), J4.B7 (D-), U1.3 (I/O2), U1.4 (I/O2)
/USB_D_P: J3.86 (USB3_HS_D_P), J4.A6 (D+), J4.B6 (D+), U1.1 (I/O1), U1.6 (I/O1)
/USB_SBU_N: J2.64 (USB_SBU_N), J4.A8 (SBU1)
/USB_SBU_P: J2.62 (USB_SBU_P), J4.B8 (SBU2)
/VREG_LX: L2.1, U4.48 (VREG_LX)
/XIN: C20.1, U4.21 (XIN), Y1.1
/XOUT: R5.2, U4.22 (XOUT)
/XTAL_O: C21.1, R5.1, Y1.3
GND: C1.2, C2.2, C3.2, C4.2, C5.2, C6.2, C7.2, C8.2, C9.2, C10.2, C11.2, C12.2, C13.2, C14.2, C15.2, C16.2, C17.2, C18.2, C19.2, C20.2, C21.2, C22.2, C23.2, C24.2, D1.1 (K), D2.1 (K), D3.1 (K), D4.1 (K), J1.1 (GND), J1.2 (GND), J1.7 (GND), J1.8 (GND), J1.13 (GND), J1.14 (GND), J1.19 (GND), J1.20 (GND), J1.25 (GND), J1.26 (GND), J1.31 (GND), J1.32 (GND), J1.37 (GND), J1.38 (GND), J1.43 (GND), J1.44 (GND), J1.49 (GND), J1.50 (GND), J1.55 (GND), J1.61 (GND), J1.74 (GND), J2.2 (GND), J2.4 (GND), J2.16 (CS_P), J2.18 (CS_N), J2.22 (VBATT_CONN_VSENSE_N), J2.60 (GND), J2.66 (GND), J2.67 (GND), J2.73 (GND), J2.79 (GND), J2.85 (GND), J3.8 (GND), J3.14 (GND), J3.20 (GND), J3.23 (GND), J3.26 (GND), J3.29 (GND), J3.32 (GND), J3.35 (GND), J3.38 (GND), J3.41 (GND), J3.47 (GND), J3.53 (GND), J3.59 (GND), J3.71 (GND), J3.77 (GND), J3.83 (GND), J3.84 (GND), J3.89 (GND), J3.90 (GND), J3.95 (GND), J3.96 (GND), J4.A1 (GND), J4.A12 (GND), J4.B1 (GND), J4.B12 (GND), J4.SH (SHIELD), J5.1, J5.4, J5.12, J5.24, J6.1, J6.22, J6.24, J7.6 (VSS), J7.10 (DET_A), J7.SH (SHIELD), R2.2, R10.2, R11.2, R14.2, R15.2, SW1.2, SW2.2, SW3.2, SW4.2, TH1.2, U1.2 (GND), U2.6 (GND), U2.7 (FSW), U2.8 (DEF), U2.15 (GND), U2.16 (GND), U2.17 (GND), U3.2 (GND), U4.47 (VREG_PGND), U4.61 (GND), U5.4 (GND), U5.9 (EP), U6.3 (GND), U7.3 (GND), Y1.2 (G), Y1.4 (G)
SD_VDD: C23.1, J3.2 (VREG_L21A_2P95), J3.4 (VREG_L21A_2P95), J3.6 (VREG_L21A_2P95), J7.4 (VDD)
SD_VIO: C24.1, J3.1 (VREG_L13A_2P95), R18.2, R19.2, R20.2, R21.2, R22.2, R23.2
SOM_SYS: C3.1, C4.1, C5.1, C7.1, J2.1 (SOM_SYS_PWR), J2.3 (SOM_SYS_PWR), J2.5 (SOM_SYS_PWR), J2.6 (SOM_SYS_PWR), J2.7 (SOM_SYS_PWR), J2.8 (SOM_SYS_PWR), J2.9 (SOM_SYS_PWR), J2.10 (SOM_SYS_PWR), J2.11 (SOM_SYS_PWR), J2.12 (SOM_SYS_PWR), J2.13 (SOM_SYS_PWR), J2.14 (SOM_SYS_PWR), J2.15 (SOM_SYS_PWR), J2.17 (SOM_SYS_PWR), J2.19 (SOM_SYS_PWR), J2.21 (SOM_SYS_PWR), J2.23 (SOM_SYS_PWR), J2.24 (VBATT_CONN_VSENSE_P), L1.2, R1.1, U2.14 (VOS), U3.1 (VIN), U3.3 (EN)
VBUS: C1.1, C2.1, J2.25 (USB_VBUS), J2.27 (USB_VBUS), J2.29 (USB_VBUS), J2.31 (USB_VBUS), J2.33 (USB_VBUS), J4.A4 (VBUS), J4.A9 (VBUS), J4.B4 (VBUS), J4.B9 (VBUS), J5.2, U1.5 (VBUS), U2.10 (VIN), U2.11 (VIN), U2.12 (VIN), U2.13 (EN)
VREG_AVDD: C11.1, R3.2, U4.46 (VREG_AVDD)

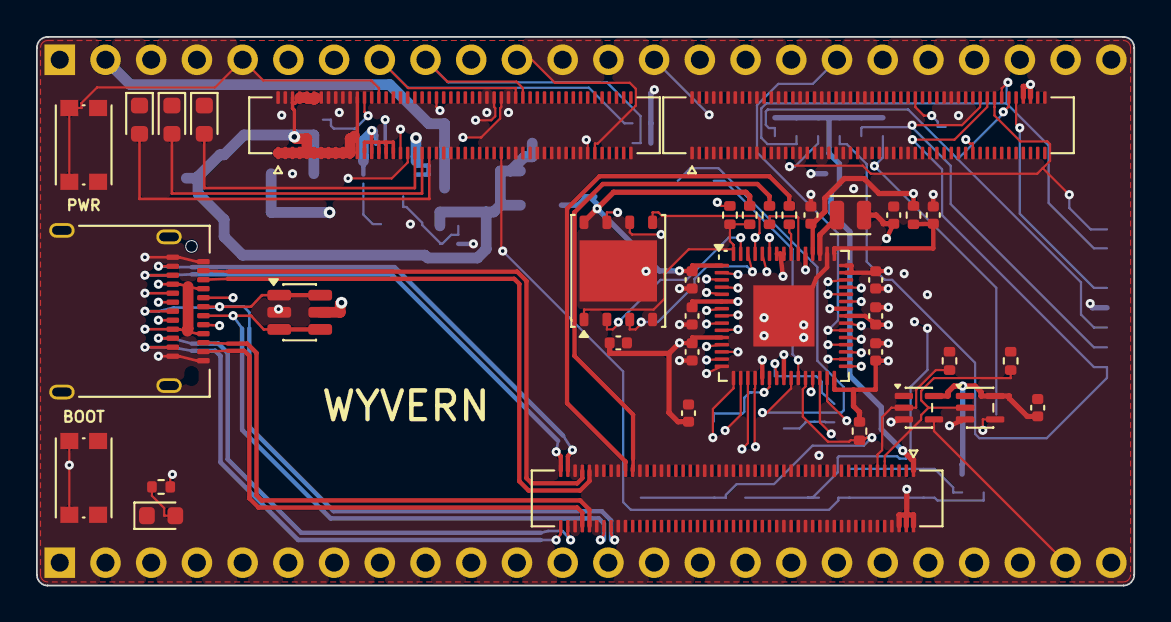
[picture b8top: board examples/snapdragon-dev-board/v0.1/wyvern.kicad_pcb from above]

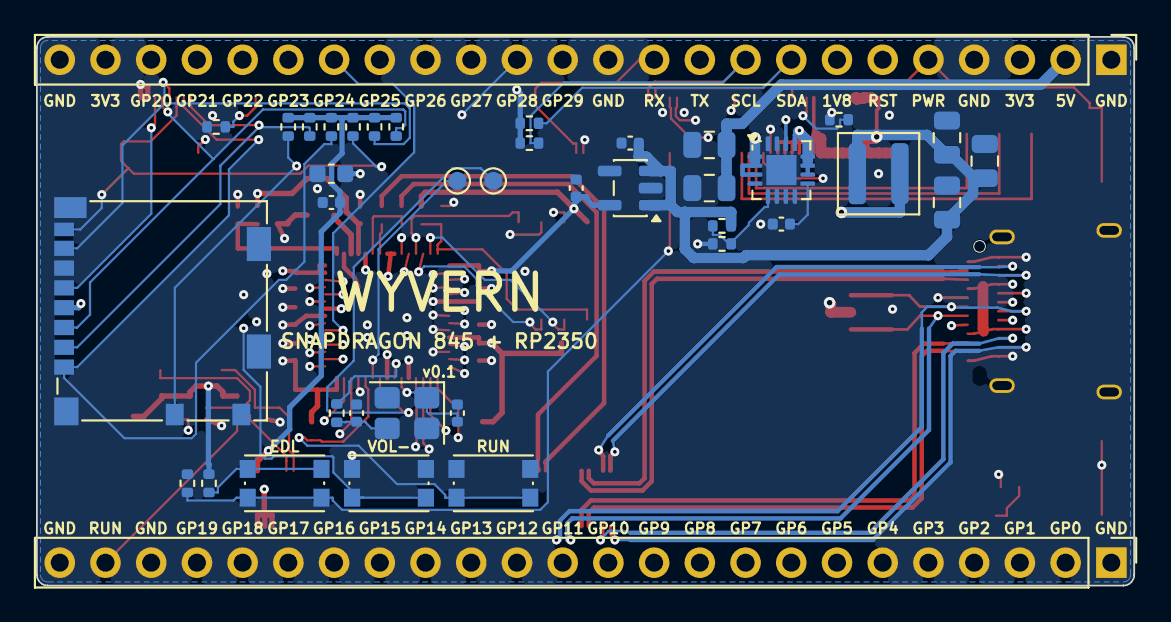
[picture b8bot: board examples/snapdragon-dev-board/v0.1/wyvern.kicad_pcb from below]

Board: 6 copper layers, 61.0 x 30.5 mm, 76 parts (39 on the bottom side), 97 nets.
